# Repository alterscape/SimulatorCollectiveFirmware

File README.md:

# Simulator Collective Firmware

This repo contains firmware for a DIY simulator collective. The intent is not to commercialize, but rather to design something usable that an interested hobbyist with a relatively limited fabrication setup (ie: yours truly) can build and customize. Because I'm an aviation simulation enthusiast who likes physically correct (or as close as I can get for affordable prices) switchology, the "head" or "button box" component is designed to be interchangeable to support different airframes' controls. So far there are two software components:

## Collective Base

This firmware is intended to run on a Teensy 3.x, with the Joystick USB profile. It uses a contactless hall effect sensor to measure the collective arm's angle, and integrates input from the interchangeable button box. In future hardware/software revisions I hope to connect a twist throttle and collective brake as well.

## Collective Button Box

This firmware interfaces switches with the Base as an I2C slave. I probably could've used 74HC165 shift registers, like the Thrustmaster Cougar/Warthog, and just put all the brains in the Collective Base, but I like the idea of being able to support joystick axes (eg: for the spotlight slew control on some DCS helicopters) and for the box to be able to report things like its intended range of motion to the base.

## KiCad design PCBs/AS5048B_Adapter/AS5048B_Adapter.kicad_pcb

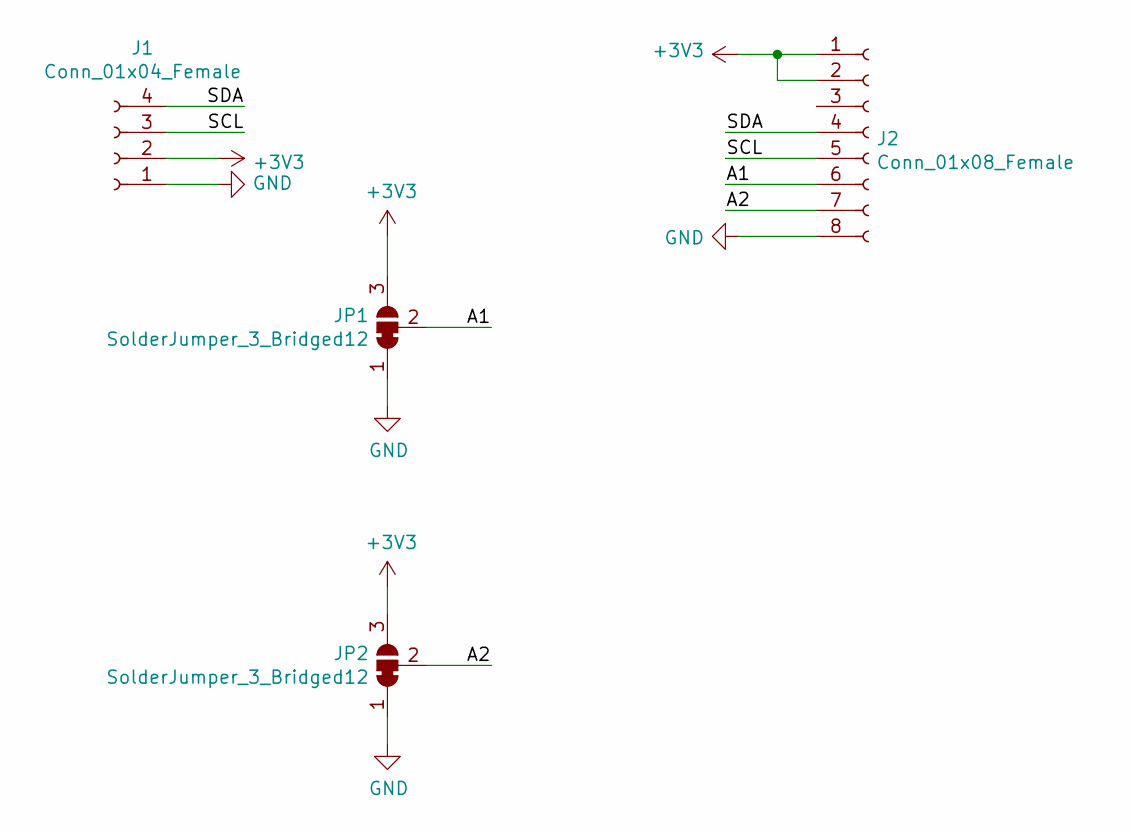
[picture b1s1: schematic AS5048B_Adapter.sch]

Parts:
J1: Conn_01x04_Female; Molex_PicoBlade_53047-0410_04x1.25mm_Straight
J2: Conn_01x08_Female; PinHeader_1x08_P2.54mm_Vertical
JP1, JP2: SolderJumper_3_Bridged12; SolderJumper-3_P1.3mm_Bridged12_Pad1.0x1.5mm

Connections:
+3V3: J1.2, J2.1, J2.2, JP1.3 (B), JP2.3 (B)
/A1: J2.6, JP1.2 (C)
/A2: J2.7, JP2.2 (C)
/SCL: J1.3, J2.5
/SDA: J1.4, J2.4
GND: J1.1, J2.8, JP1.1 (A), JP2.1 (A)

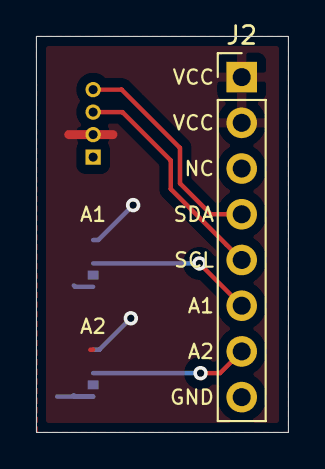
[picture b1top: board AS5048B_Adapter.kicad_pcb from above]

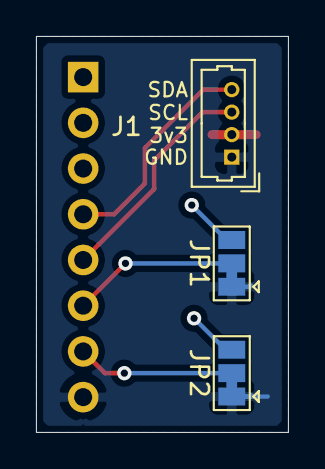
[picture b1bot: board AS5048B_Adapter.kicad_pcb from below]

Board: 2 copper layers, 14.0 x 22.0 mm, 4 parts (3 on the bottom side), 6 nets.

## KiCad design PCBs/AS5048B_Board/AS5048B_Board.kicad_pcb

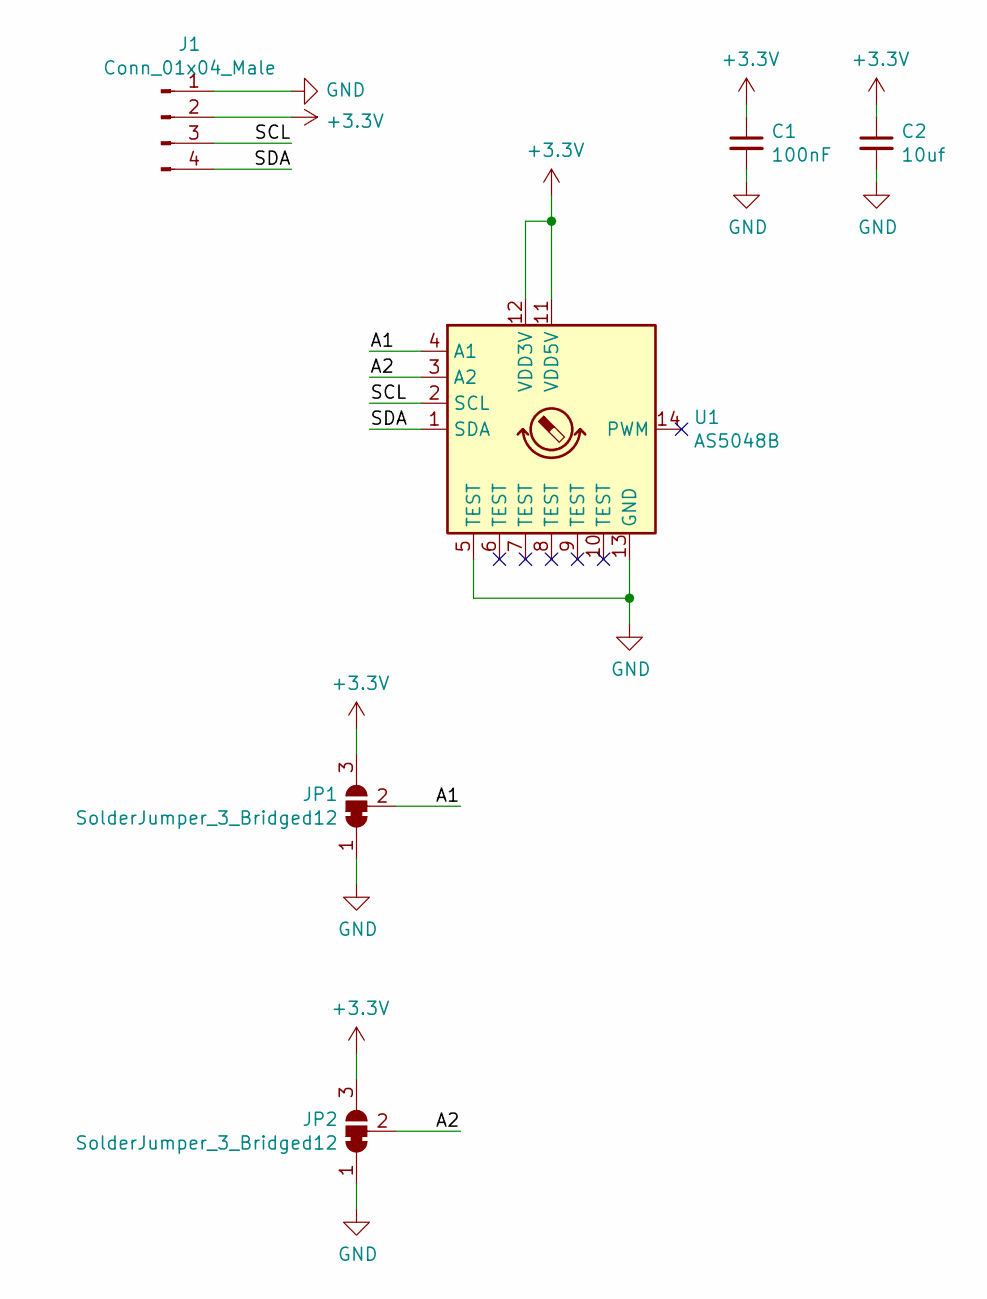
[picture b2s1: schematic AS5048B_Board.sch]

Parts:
C1: 100nF; C_0603_HandSoldering
C2: 10uf; C_0603_HandSoldering
J1: Conn_01x04_Male; Molex_PicoBlade_53047-0410_04x1.25mm_Straight
JP1, JP2: SolderJumper_3_Bridged12; SolderJumper-3_P1.3mm_Bridged12_Pad1.0x1.5mm
U1: AS5048B; TSSOP-14_4.4x5mm_P0.65mm

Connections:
+3V3: C1.1, C2.1, J1.2, JP1.3 (B), JP2.3 (B), U1.11 (VDD5V), U1.12 (VDD3V)
/A1: JP1.2 (C), U1.4 (A1)
/A2: JP2.2 (C), U1.3 (A2)
/SCL: J1.3, U1.2 (SCL)
/SDA: J1.4, U1.1 (SDA)
GND: C1.2, C2.2, J1.1, JP1.1 (A), JP2.1 (A), U1.5 (TEST), U1.13 (GND)

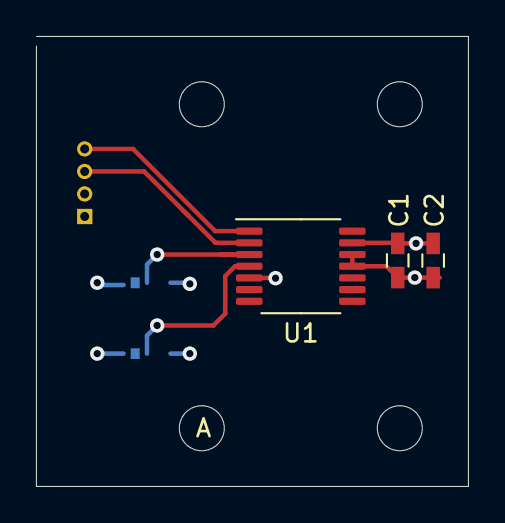
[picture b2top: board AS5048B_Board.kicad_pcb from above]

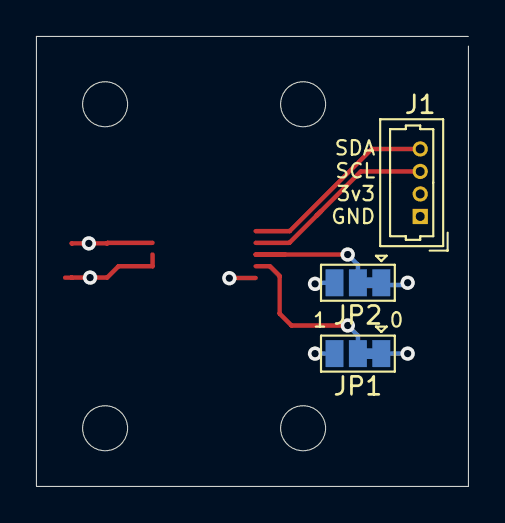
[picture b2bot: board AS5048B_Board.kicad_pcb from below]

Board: 4 copper layers, 24.0 x 25.0 mm, 8 parts (3 on the bottom side), 6 nets.

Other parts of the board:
A: MountingHole_2.5mm
B: MountingHole_2.5mm

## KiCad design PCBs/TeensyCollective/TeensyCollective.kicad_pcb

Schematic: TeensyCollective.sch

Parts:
C1: 47u; CP_Elec_4x4.5
C2, C4: 0.1uf; C_0603_HandSoldering
C3, C5: 1uf; C_0603_HandSoldering
D1: 1N4001; D_DO-41_SOD81_P7.62mm_Horizontal
FB1: Tiny; R_0603_HandSoldering
H1, H2, H3: MountingHole; MountingHole_2.2mm_M2_DIN965
J1: Barrel_Jack_MountingPin; BARREL_JACK
J2, J7: Conn_01x03; Molex_PicoBlade_53047-0310_03x1.25mm_Straight
J3, J4, J6: Conn_01x04; Molex_PicoBlade_53047-0410_04x1.25mm_Straight
J5: Conn_01x02; PinHeader_1x02_P2.54mm_Vertical
Q1: FQP30N06L; TO-220
R1, R2: 470; R_0603_HandSoldering
R3: R_Small_US; R_0603_HandSoldering
R4: 10k; R_0603_HandSoldering
R5, R6: 0; R_0603_HandSoldering
U1: Teensy3.2; Teensy30_31_32_LC_EDGE_ONLY

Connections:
+3V3: C2.1, C5.1, J2.2, J3.2, J4.2, J6.2, J7.2, R1.1, R2.2, U1.31
+5V: C1.1, D1.1, FB1.1, J1.1, J5.1
/BRAKE_PWM: R3.2, U1.8
/I1: J2.3, R6.1
/I2: J7.3, R5.2
/SCL: J3.3, J4.3, J6.3, R2.1, U1.26
/SDA: J3.4, J4.4, J6.4, R1.2, U1.25
GND: C1.2, C2.2, C3.2, C4.2, C5.2, J1.2, J2.1, J3.1, J4.1, J6.1, J7.1, Q1.3, R4.1, U1.1
unnamed: C3.1, C4.1, FB1.2, U1.33
unnamed: D1.2, J5.2, Q1.2
unnamed: Q1.1, R3.1, R4.2
unnamed: R5.1, U1.9
unnamed: R6.2, U1.10

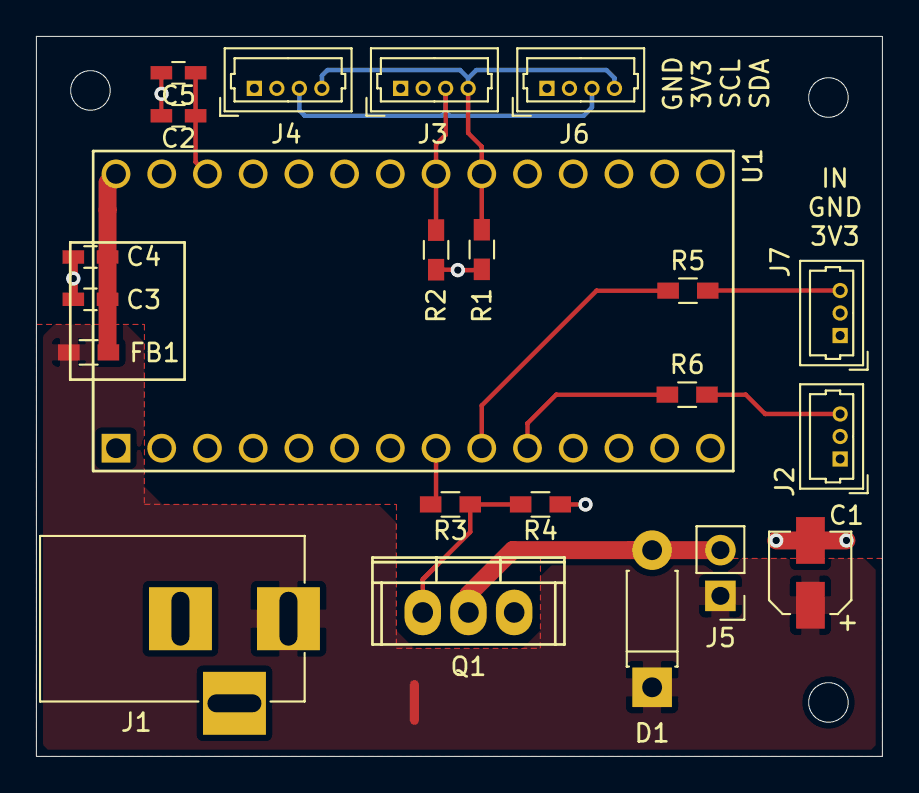
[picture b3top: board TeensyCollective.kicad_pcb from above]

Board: 4 copper layers, 47.0 x 40.0 mm, 25 parts (0 on the bottom side), 13 nets.

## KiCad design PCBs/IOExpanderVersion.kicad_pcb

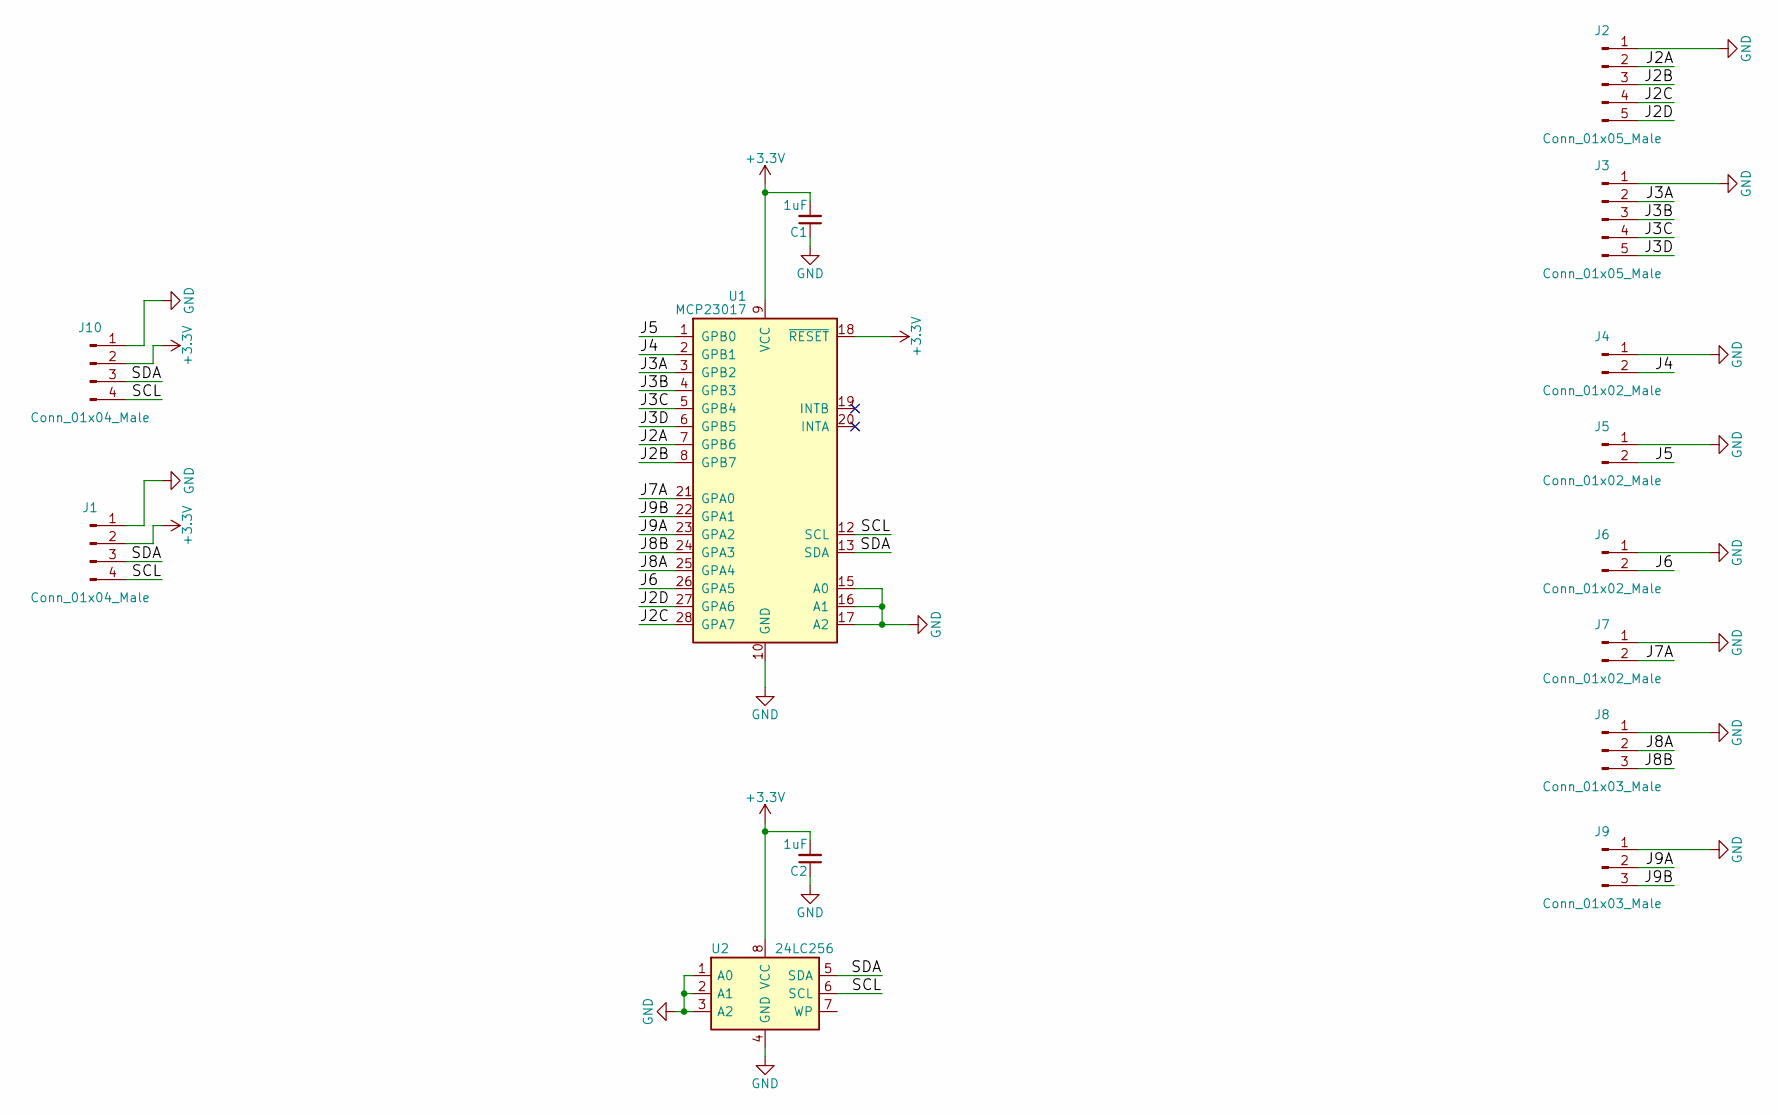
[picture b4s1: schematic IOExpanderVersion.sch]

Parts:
C1, C2: 1uF; C_0805_HandSoldering
J1, J10: Conn_01x04_Male; Molex_PicoBlade_53047-0410_04x1.25mm_Straight
J2, J3: Conn_01x05_Male; Molex_PicoBlade_53047-0510_05x1.25mm_Straight
J4, J5, J6, J7: Conn_01x02_Male; Molex_PicoBlade_53047-0210_02x1.25mm_Straight
J8, J9: Conn_01x03_Male; Molex_PicoBlade_53047-0310_03x1.25mm_Straight
U1: MCP23017; SOIC-28
U2: 24LC256; SOIC-8_3.9x4.9mm_Pitch1.27mm

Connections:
+3V3: C1.2, C2.2, J1.2, J10.2, U1.9 (VCC), U1.18 (~RESET), U2.8 (VCC)
/J2A: J2.2, U1.7 (GPB6)
/J2B: J2.3, U1.8 (GPB7)
/J2C: J2.4, U1.28 (GPA7)
/J2D: J2.5, U1.27 (GPA6)
/J3A: J3.2, U1.3 (GPB2)
/J3B: J3.3, U1.4 (GPB3)
/J3C: J3.4, U1.5 (GPB4)
/J3D: J3.5, U1.6 (GPB5)
/J4: J4.2, U1.2 (GPB1)
/J5: J5.2, U1.1 (GPB0)
/J6: J6.2, U1.26 (GPA5)
/J7A: J7.2, U1.21 (GPA0)
/J8A: J8.2, U1.25 (GPA4)
/J8B: J8.3, U1.24 (GPA3)
/J9A: J9.2, U1.23 (GPA2)
/J9B: J9.3, U1.22 (GPA1)
/SCL: J1.4, J10.4, U1.12 (SCL), U2.6 (SCL)
/SDA: J1.3, J10.3, U1.13 (SDA), U2.5 (SDA)
GND: C1.1, C2.1, J1.1, J2.1, J3.1, J4.1, J5.1, J6.1, J7.1, J8.1, J9.1, J10.1, U1.10 (GND), U1.15 (A0), U1.16 (A1), U1.17 (A2), U2.1 (A0), U2.2 (A1), U2.3 (A2), U2.4 (GND)

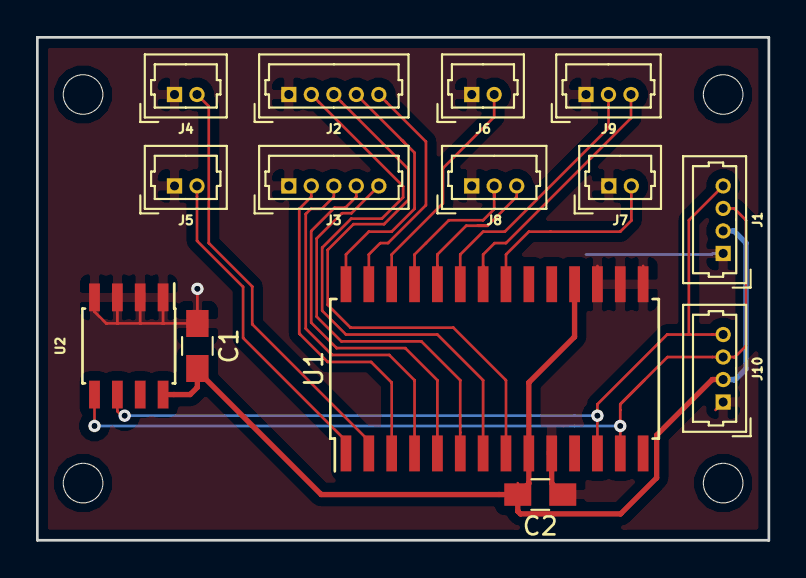
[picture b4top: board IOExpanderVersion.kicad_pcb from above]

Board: 2 copper layers, 40.6 x 27.9 mm, 14 parts (0 on the bottom side), 20 nets.

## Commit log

2018-02-28 Added readme and Arduino sketches.
2018-03-11 Add I2C protocol for interchangeable button boxes.
    Super simple for now, but room to grow!
2018-06-26 The version I actually sent to fab!
2019-04-14 Split angle sensor and GPIO into methods. Fixed GPIO.
2019-04-14 Updated to new kicad 5.x
2021-07-11 Initial commit of TeensyCollective v0
2021-07-28 Add serial control for range and brake strength; iterate PCBs.
